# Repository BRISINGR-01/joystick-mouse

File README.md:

# Joystick Mouse Prototype

## Overview

This project demonstrates a simple joystick-based mouse using an Arduino and Python. The Arduino reads a 2-axis joystick and a button, sending X/Y movement and click state over serial. A Python script interprets the data and moves the system cursor using ydotool.

The goal is to create a keyboard-adjacent pointing device as an alternative to a traditional mouse.

## Hardware Requirements

- Arduino Nano (or compatible board)
- 2-axis analog joystick
- Push button (for primary click)
- USB cable for serial connection

## Connections
- Joystick X → A2
- Joystick Y → A4
- Button → A1 (with INPUT_PULLUP)

## Software Requirements
- Python 3
- ezButton library (Arduino)
- ydotool (Linux)

### What it does
- Reads joystick axes and button state
- Maps analog joystick values to a range of -MOUSE_SENSITIVITY to MOUSE_SENSITIVITY
- Applies a small deadzone to avoid drift
- Sends data over serial in the format:
- X_value:Y_value:button_state

#### Python Script

- Opens serial port to Arduino (/dev/ttyUSB0)
- Reads and parses serial data
- Moves cursor with ydotool according to X/Y values
- Triggers mouse click on button press

#### Behavior
- Joystick movement → cursor movement
- Button press → left mouse click
- Supports continuous movement with adjustable delay (time.sleep(0.02))

## Usage

0) Install ydotool and ensure permissions allow cursor control.
  
1) Connect Arduino to PC and upload the sketch. Might have to unlock port with
```
chmod 777 /dev/ACM*  
chmod 777 /dev/tty*
```
2) Set up the python environment. Ex: `pip install pyserial`

3) Set the port in the python script and run it with:

`python3 joystick_mouse.py`

Move the joystick to control the cursor; press the button to click.

## Notes

Sensitivity and deadzone can be adjusted in the Arduino sketch (MOUSE_SENSITIVITY and threshold).

The script currently uses Linux-specific ydotool; adaptation is needed for other OSes.

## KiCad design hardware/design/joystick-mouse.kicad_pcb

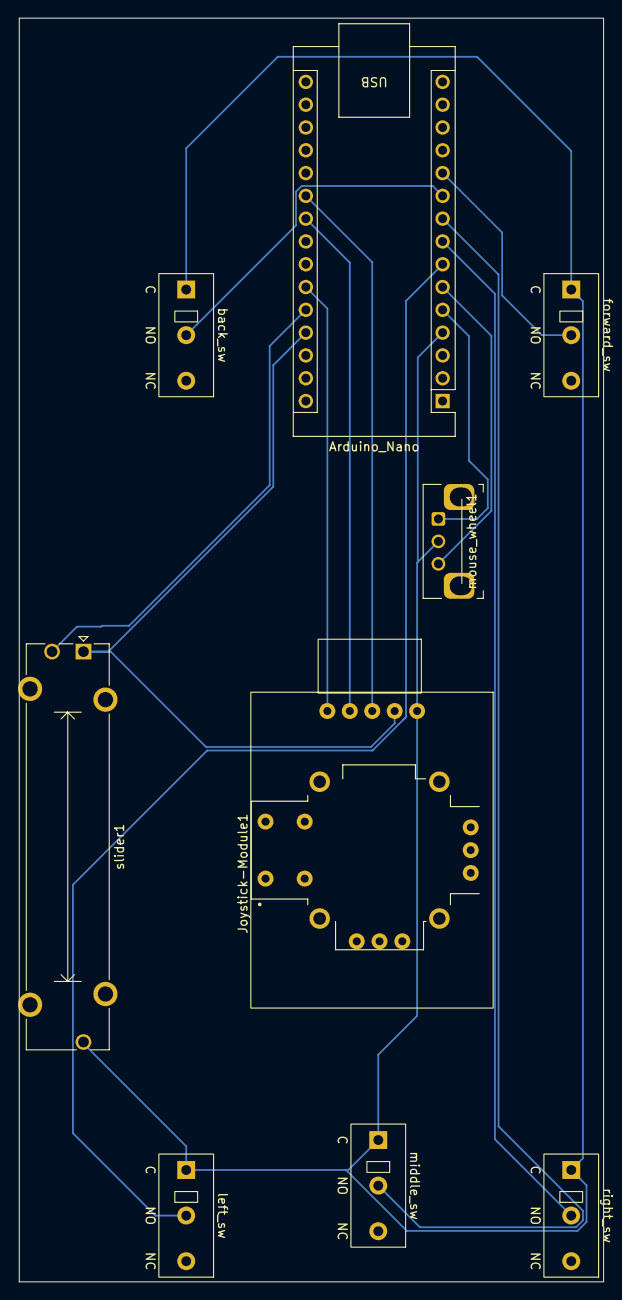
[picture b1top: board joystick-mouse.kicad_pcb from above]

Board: 2 copper layers, 65.1 x 140.8 mm, 9 parts (0 on the bottom side), 13 nets.

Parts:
Arduino_Nano: Arduino_Nano
Joystick-Module1: ky-023_joystick
back_sw: SW_SPST; SW_XKB_DM1-16UP-1
forward_sw: SW_SPST; SW_XKB_DM1-16UP-1
left_sw: SW_SPST; SW_XKB_DM1-16UP-1
middle_sw: SW_SPST; SW_XKB_DM1-16UP-1
mouse_wheel1: RotaryEncoder; RotaryEncoder_Bourns_Horizontal_PEC12R-2x17F-Nxxxx
right_sw: SW_SPST; SW_XKB_DM1-16UP-1
slider1: Potentiometer; Potentiometer_Bourns_PTA3043_Single_Slide

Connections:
+5V: Arduino_Nano.27 (+5V), Joystick-Module1.2 (VCC), slider1.1
GND: Arduino_Nano.4 (GND), Arduino_Nano.29 (GND), Joystick-Module1.1 (GND), back_sw.1 (A), forward_sw.1 (A), left_sw.1 (A), middle_sw.1 (A), mouse_wheel1.C, right_sw.1 (A), slider1.3
unnamed: Arduino_Nano.21 (A2), Joystick-Module1.3 (VRx)
unnamed: Arduino_Nano.22 (A3), Joystick-Module1.4 (VRy)
unnamed: Arduino_Nano.25 (A6), Joystick-Module1.5 (SW)
unnamed: Arduino_Nano.26 (A7), slider1.2
unnamed: Arduino_Nano.5 (D2), mouse_wheel1.A
unnamed: Arduino_Nano.6 (D3), mouse_wheel1.B
unnamed: Arduino_Nano.7 (D4), left_sw.2 (B)
unnamed: Arduino_Nano.8 (D5), right_sw.2 (B)
unnamed: Arduino_Nano.9 (D6), middle_sw.2 (B)
unnamed: Arduino_Nano.10 (D7), back_sw.2 (B)
unnamed: Arduino_Nano.11 (D8), forward_sw.2 (B)

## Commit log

2026-03-30 create uiinput driver
2026-03-30 document
2026-04-02 abstract uinput from mouse into a composition via an abstract interface
2026-04-05 rotary + joystick
2026-04-16 add protbuf
2026-05-17 epoll
2026-05-19 communication
2026-05-19 hot plug in
2026-05-19 add logs
2026-06-08 unit tests
2026-06-11 finish pcb
